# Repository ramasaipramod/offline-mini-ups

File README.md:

# Offline Mini UPS

This project involves designing a 3-section Offline Mini UPS with the following functionalities:

1. **Inverter Section and Mains-Inverter Changeover Section**  
   Ensures power transition between mains and inverter.

2. **Oscillator Section**  
   Generates the required oscillation for the offline UPS.

3. **Battery Status Indicator Section**  
   Displays the charge status of the connected 12V battery.

## Files in the Repository

### EAGLE Files
- **`EP Project.brd`**: PCB layout design.  
- **`EP Project.sch`**: Schematic diagram of the circuit.

### EasyEDA Files
- **`PCB.json`**: PCB design in JSON format.  
- **`info`**: Project metadata.  
- **`project.json`**: Full project configuration file.

## Components Used
- **Passive Components**: Resistors and capacitors with various values.  
- **Integrated Circuits**: Dual JK Flip-Flop, 555 Timer.  
- **Transistors**: NPN and PNP types.  
- **Diodes**: Rectifier diodes, Zener diodes.  
- **Other Components**:  
  - LED, neon lamp.  
  - Transformer, relay, and 12V battery.  
  - 2-pin connector and ON/OFF switch.

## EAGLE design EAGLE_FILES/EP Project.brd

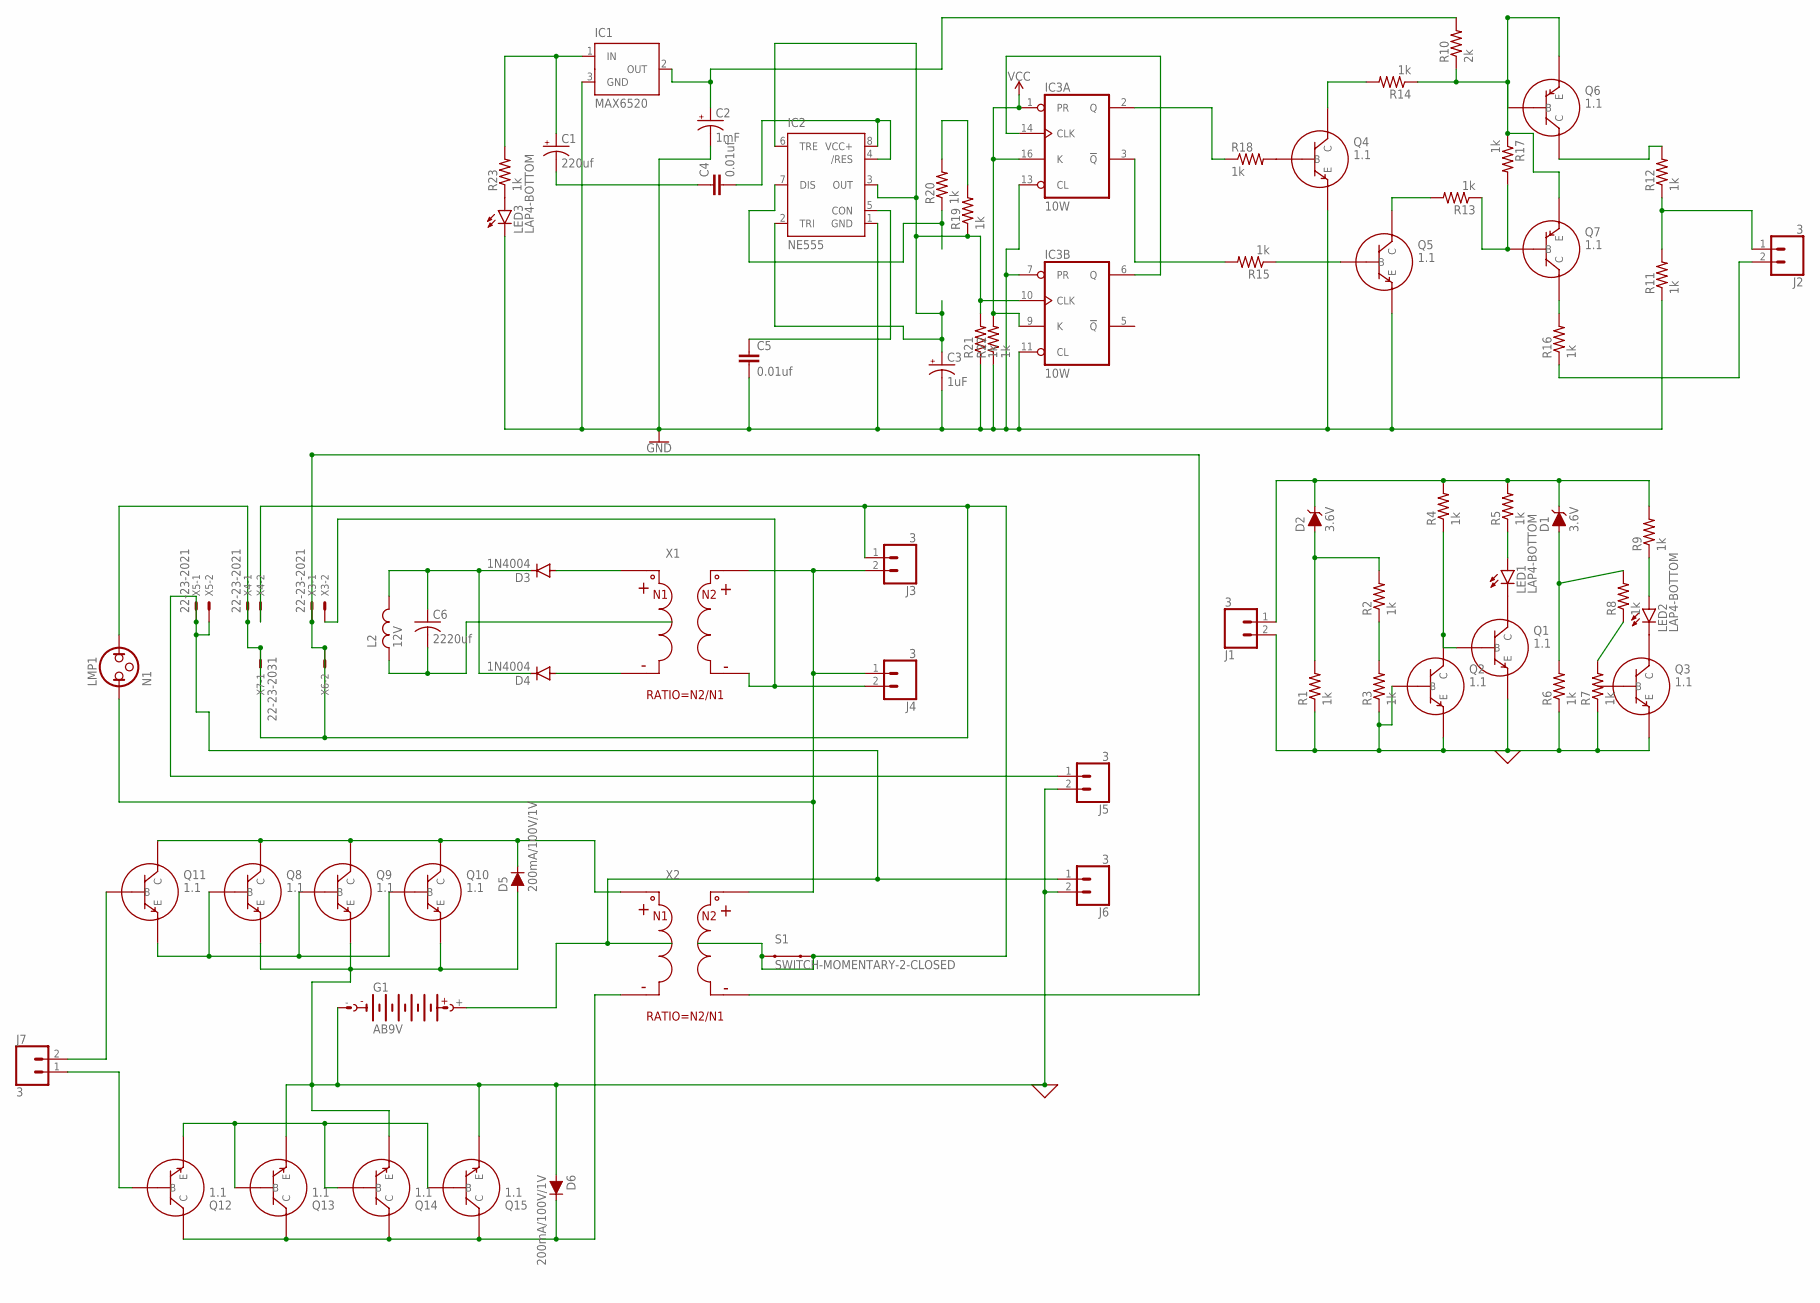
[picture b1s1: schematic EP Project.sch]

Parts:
C1: 220uf; CPOL-RADIAL-5MM-10MM
C2: 1mF; CPOL-RADIAL-5MM-10MM
C3: 1uF; CPOL-RADIAL-5MM-10MM
C4, C5: 0.01uf; 0402-TIGHT
C6: 2220uf; C025-024X044
D1, D2: 3.6V; SOD-323
D3, D4: 1N4004; DO41-10
D5, D6: 200mA/100V/1V; DIODE-1N4148
G1: AB9V
IC1: MAX6520; SOT23
IC2: NE555; DIL-08
IC3: 10W; DIL16
J1, J2, J3, J4, J5, J6, J7: 3; 1X02
LED1, LED2, LED3: LAP4-BOTTOM; P47F-BOTTOM
LMP1: N1; LDH-3R
R1, R2, R3, R4, R5, R6, R7, R8, R9, R11, R12, R13, R14, R15, R17, R18, R19, R20, R21, R22, R23: 1k; 0204/5
R10: 2k; 0204/5
R16: 1k; 0204/7
S1: SWITCH-MOMENTARY-2-CLOSED; TACTILE-PTH-12MM
X3, X4, X5: 22-23-2021
X6, X7: 22-23-2031

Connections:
0: D5.A, D6.A, G1.-, J1.2, J5.2, J6.2, R1.1, R3.1, R6.1, R7.1
GND: C2.-, C3.-, C5.2, IC1.3 (GND), IC2.1 (GND), IC3.4 (GND), IC3.7 (PR), IC3.11 (CL), IC3.13 (CL), LED3.C, R11.1, R21.1, R22.1
unnamed: D1.C, D2.C, J1.1, R4.2, R5.2, R9.2
unnamed: D2.A, R1.2, R2.2
unnamed: LED1.A, R5.1
unnamed: D1.A, R6.2, R8.2
unnamed: R7.2, R8.1
unnamed: LED2.A, R9.1
unnamed: R2.1, R3.2
unnamed: G1.+, J5.1, J6.1, X5.1, X5.2
unnamed: C1.+, IC1.1 (IN), R23.2
unnamed: C5.1, IC2.5 (CON)
unnamed: C2.+, IC1.2 (OUT), R10.2
unnamed: C1.-, C4.1
unnamed: C4.2, IC2.4 (/RES), IC2.8 (VCC+)
unnamed: R19.2, R20.2
unnamed: LED3.A, R23.1
unnamed: IC2.7 (DIS), R20.1
unnamed: C3.+, IC2.2 (TRI), IC2.3 (OUT), IC2.6 (TRE), IC3.10 (CLK), R19.1, R21.2
unnamed: R10.1, R14.1, R17.1
unnamed: IC3.6 (Q), IC3.14 (CLK)
unnamed: C6.1, D3.C, D4.C
unnamed: IC3.2 (Q), R18.1
unnamed: IC3.3 (!Q), R15.2
unnamed: R13.1, R17.2
unnamed: J2.1, R11.2, R12.1
unnamed: J2.2, R16.1
unnamed: J3.2, J4.1, LMP1.1
unnamed: J4.2, X3.2
unnamed: J3.1, LMP1.2, S1.1, S1.3 (2), X3.1, X4.1, X4.2, X6.2, X7.1
VCC: IC3.1 (PR), IC3.9 (K), IC3.12 (VCC), IC3.16 (K), R22.2

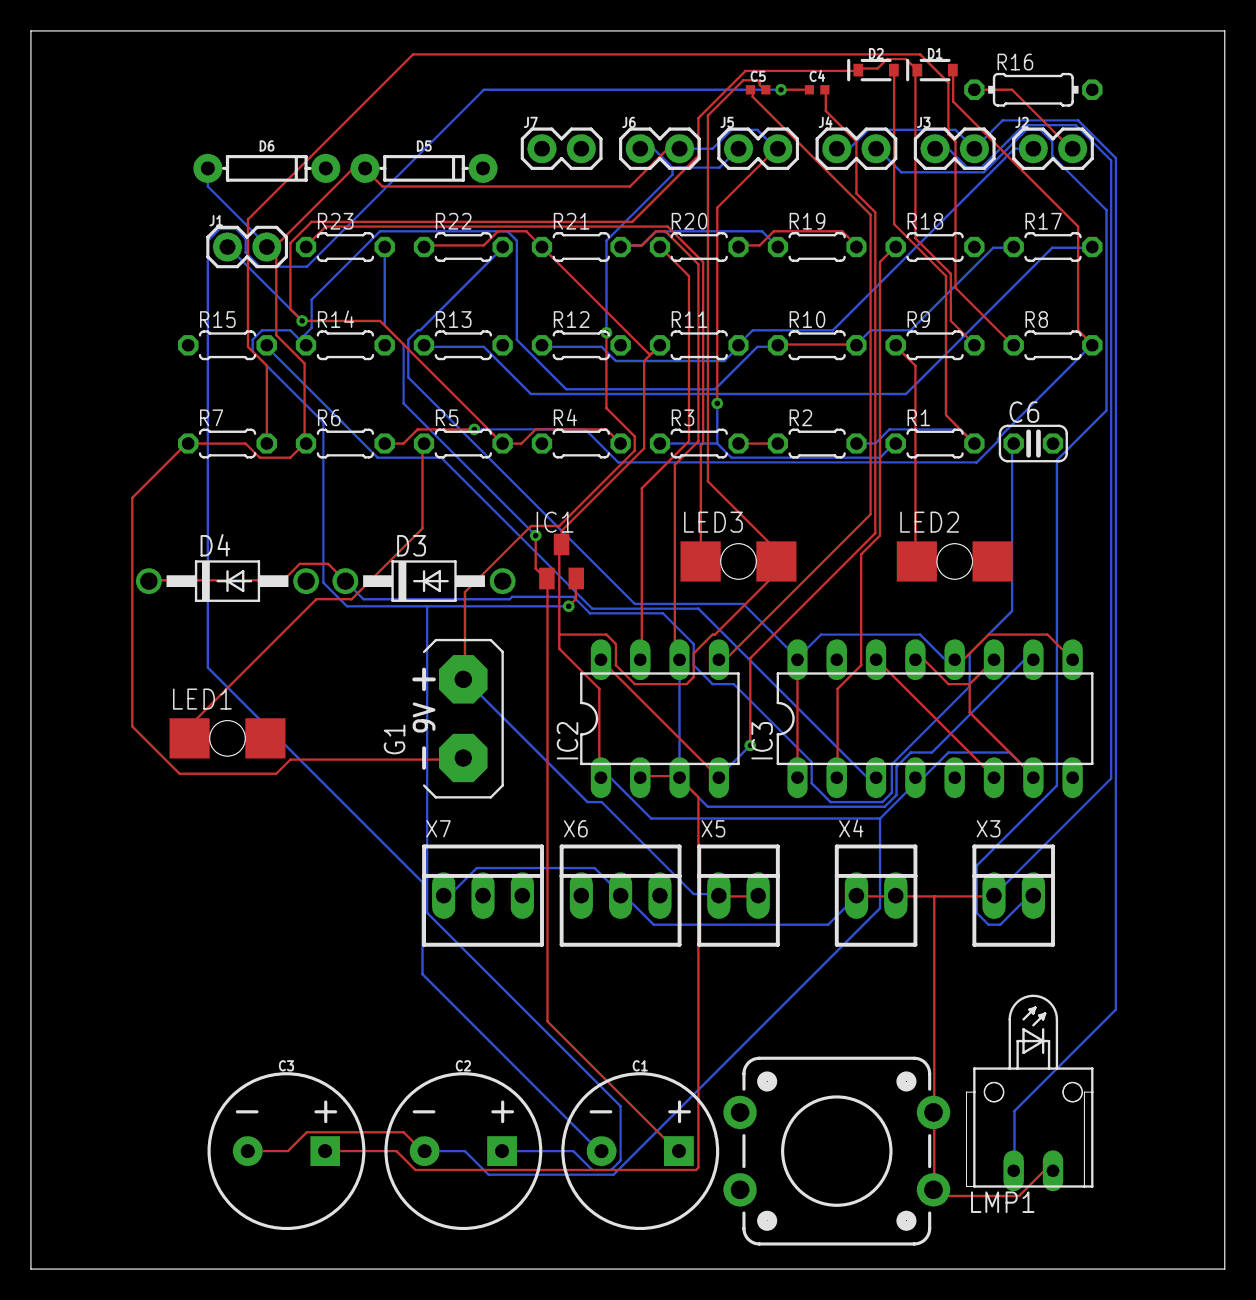
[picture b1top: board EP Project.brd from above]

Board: 2 copper layers, 77.1 x 80.0 mm, 56 parts (0 on the bottom side), 31 nets.

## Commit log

2024-12-23 Initial commit with all files

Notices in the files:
parts and their libraries:
SparkFun-Capacitors: Licensing: Creative Commons ShareAlike 4.0 International - https://creativecommons.org/licenses/by-sa/4.0
